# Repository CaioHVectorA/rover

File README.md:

# 🤖 Rover Móvel ESP32-S3 4WD & Pan/Tilt VR

Robô explorador terrestre com **tração integral 4WD**, cabeça articulada **Pan/Tilt** com streaming de vídeo de baixa latência e controle mobile imersivo via **Realidade Virtual (VR Head-Tracking)**.

---

### 🟢 Status do Projeto: **Robô montado & Testes práticos em andamento**
* **Hardware (V1 Montado):** Robô montado fisicamente (chassi 3D protótipo, rodas de 32 mm com 8 mm de vão livre, placa perfurada concluída).
* **Próxima Geração (PCB V2):** Transição direta para a PCB definitiva ([`rover_pcb_v2_chassi`](docs/hardware/kicad/rover_pcb_v2_chassi/MONTAGEM_3D.md)) com **ESP32 interno no chassi**, comunicação via **UART Serial Direta 3.3V** e áudio I2S (`INMP441` + `MAX98357A`).
* **Firmware & Visão:** ESP32-S3 e Nano operacionais com visão computacional (modo apresentador / gestos) em testes práticos.
* **Próximo passo:** Fabricar/montar a PCB V2, ajustar o chassi 3D para a nova placa e implementar o pipeline de vídeo UDP + servidor de IA.

---

## 🏗️ Arquitetura do Sistema

O projeto adota uma arquitetura **distribuída em 2 microcontroladores**, interligados por um chicote ultra-flexível de **apenas 3 a 4 fios**:

```mermaid
flowchart TD
    subgraph APP["📱 App Mobile (Expo / React Native) / Navegador Web"]
        VR["Modo VR Head-Tracking / FPV"]
        WS_CLI["WebSocket Client (JSON ou ASCII @ 35Hz)"]
        STREAM_CLI["Player de Vídeo MJPEG (:82/stream)"]
    end

    subgraph CABECA["📸 Cabeça Móvel (Pan / Tilt)"]
        ESP["ESP32-S3-CAM (Wi-Fi + Câmera 5MP OV5640)"]
        HTTPD["esp_http_server Dedicado no Core 0 (:82)"]
        CAM_PWR["Soneca Térmica no Reg. 0x3008"]
    end

    subgraph CHASSI["⚡ Chassi Fixo Inferior"]
        STEP["Mini 560 (5V / até 5A)"]
        BAT["Bateria Li-Ion 2S (7.4V 2500mAh)"]
        NANO["Arduino Nano V3 (5V Nativo)"]
        DRIVER["Driver TB6612FNG (MOSFET Duplo)"]
        MOTORES["4x Motores DC JGA16-050"]
        SERVOS["2x Micro Servos SG90 (Pan/Tilt)"]
        RAMPA["Rampa Soft-Start & Dead-Time"]
    end

    APP <== "Wi-Fi (Portas 80, 81 e 82)" ==> ESP
    BAT --> STEP
    BAT --> DRIVER

    %% Chicote Flexível
    STEP -.->|"Fio 1: 5.0V (Potência)"| ESP
    NANO -.->|"Fio 2: GND Comum"| ESP
    ESP -.->|"Fio 3: IO43 TX -> Nano D2 RX (via BC337 ou D0 direto)"| NANO
    NANO -.->|"Fio 4 (Opcional): Nano D1 TX -> Divisor 1k/2k -> IO44 RX"| ESP

    NANO --> DRIVER --> MOTORES
    NANO --> SERVOS
```

---

## 🔬 Suíte dos 6 POCs (Testes de Bancada Independentes)

Cada subsistema foi desacoplado para testes isolados e seguros:

| POC | Descrição | Placa & Ambiente | O que testa / resolve |
|---|---|---|---|
| **POC 1** | [Enlace Serial RX/TX](file:///c:/Users/caihe/Documents/develop/rover/docs/pocs/GUIA_EXECUCAO_POCS.md#poc-1-teste-de-enlace-serial-rxtx-com-servidor-web) | `poc1_esp32` + `poc1_nano` | Medição de ping/RTT, taxa de entrega de 100% e diagnóstico de reset do Nano |
| **POC 2** | [Pan/Tilt Controlado (Sem Vídeo)](file:///c:/Users/caihe/Documents/develop/rover/docs/pocs/GUIA_EXECUCAO_POCS.md#poc-2-pantilt-controlado-sem-v%C3%ADdeo) | `poc2_esp32` + `poc2_nano` | Eliminação do "rebolado" via interpolação em microssegundos (50 Hz) e varredura lenta |
| **POC 3** | [Transmissão de Vídeo Fria](file:///c:/Users/caihe/Documents/develop/rover/docs/pocs/GUIA_EXECUCAO_POCS.md#poc-3-transmiss%C3%A3o-de-v%C3%ADdeo-fria-esp32-isolado) | `poc3_esp32` | Soneca no reg. `0x3008`, XCLK adaptativo (8–12 MHz) e servidor no Core 0 (câmera fria) |
| **POC 4** | [Pan/Tilt + Transmissão](file:///c:/Users/caihe/Documents/develop/rover/docs/pocs/GUIA_EXECUCAO_POCS.md#poc-4-pantilt--transmiss%C3%A3o-desempenho-da-imagem) | `poc4_esp32` + `poc2_nano` | Operação simultânea com modo Eco automático (cai para 5 FPS parado) e zero bloqueio |
| **POC 5** | [Teste Automático dos Motores](file:///c:/Users/caihe/Documents/develop/rover/docs/pocs/GUIA_EXECUCAO_POCS.md#poc-5-teste-autom%C3%A1tico-de-motores-4wd-bancada-com-rodas-no-ar) | `poc5_nano` (baud 115200) | Sequência autônoma de vai-e-volta, giros e rampa com medição de queda (*sag*) de bateria |
| **POC 6** | [Motores Controlados](file:///c:/Users/caihe/Documents/develop/rover/docs/pocs/GUIA_EXECUCAO_POCS.md#poc-6-motores-controlados-joystick-virtual--teclado) | `poc6_esp32` + `poc6_nano` | Pilotagem manual (joystick touch / teclado WASD), watchdog de 600ms e rampa anti-reset |

📖 **Consulte o [Guia Completo de Execução dos POCs](file:///c:/Users/caihe/Documents/develop/rover/docs/pocs/GUIA_EXECUCAO_POCS.md)** para instruções de compilação, gravação e checklist.

---

## 📂 Organização Limpa da Codebase

```
rover/
├── README.md                      # Visão geral, arquitetura e quickstart
├── AGENTS.md                      # Diretrizes obrigatórias e regras para agentes de IA
├── style.md                       # Perfil de engenharia, tom de bancada e preferências
├── platformio.ini                 # Configuração unificada de build de todos os ambientes
│
├── docs/                          # Documentação técnica central
│   ├── context.md                 # 📖 Memória técnica contínua e histórico completo do projeto
│   ├── pocs/                      # Documentação da suíte de 6 POCs incrementais
│   │   ├── README.md              # Índice dos POCs e tabela de ambientes
│   │   └── GUIA_EXECUCAO_POCS.md  # Manual prático de gravação e teste passo a passo
│   ├── hardware/                  # Especificações técnicas, desenhos com cotas e pinagens
│   │   ├── ESPECIFICACOES_TECNICAS.md
│   │   ├── tabela_pinagem_esp32_nano.xlsx
│   │   ├── PROJETO_CONEXOES_PLACA_PERFURADA.docx
│   │   ├── kicad/                 # Projetos de circuitos e esquemáticos KiCad
│   │   └── *.png                  # Desenhos técnicos oficiais (JGA-050, SG90, StickyMAX)
│   ├── guides/                    # Guias de engenharia aprofundados
│   │   ├── camera_calor_software.md          # ❄️ Otimização térmica do OV5640 via software
│   │   ├── ajuste_fino_servos_rebolado.md    # 🎯 Física e eliminação do rebolado nos servos SG90
│   │   ├── tracao_motores_anti_reset.md      # ⚡ Prevenção de Brown-Out e rampa 4WD na TB6612
│   │   ├── controle_servos_head_tracking_vr.md # Guia didático de servos e VR Head-Tracking
│   │   ├── http_vs_websocket_redes.md        # Análise comparativa de protocolos de rede
│   │   └── streaming_video_baixa_latencia.md # Pipeline de vídeo MJPEG e baixa latência
│   ├── compras/                   # Histórico de compras, orçamentos e fotos das lojas
│   └── references/                # Fotos reais dos produtos e montagens maker de referência
│
├── src/                           # Código-fonte do projeto
│   ├── firmware/                  # Códigos C++ / Arduino organizados por módulo
│   │   ├── comum/                 # Módulos compartilhados reutilizáveis (câmera, enlace, rampa, servos)
│   │   ├── pocs/                  # Códigos-fonte dos 6 POCs isolados
│   │   ├── gateway_app/           # Firmware de produção integrado ao App Mobile Expo
│   │   └── legado/                # Sketches e testes históricos arquivados
│   ├── app_mobile/                # Aplicativo Expo / React Native (VR, FPV e Dashboard)
│   └── servidor_relay/            # Servidor Node.js / Docker para teleoperação em nuvem
│
└── tools/                         # Ferramentas auxiliares e geradores Python
    └── scratch/                   # Scripts utilitários de apoio
```

---

## ⚡ Comandos de Compilação e Gravação (PlatformIO)

Substitua `COMx` pelas portas seriais reais conectadas:

```powershell
# Gravação do ESP32-S3 (Exemplo POC 4: Pan/Tilt + Câmera):
pio run -e poc4_esp32 -t upload --upload-port COM24

# Gravação do Arduino Nano (Exemplo POC 2/4: Servos Suaves):
pio run -e poc2_nano -t upload --upload-port COM18

# Teste autônomo dos motores (POC 5):
pio run -e poc5_nano -t upload --upload-port COM18
pio device monitor -e poc5_nano --port COM18
```

---

## ⚙️ Componentes Físicos Adquiridos & Validados

| Componente | Modelo / Especificação | Função no Rover |
| :--- | :--- | :--- |
| **Motores de Tração** | 4x **JGA16-050** (16mm, redução metálica, eixo D 3mm) | Tração 4WD com torque elevado |
| **Rodas** | 4x **Rodas 32 mm** com cubo de fixação | Diâmetro externo de 32 mm elevando o vão livre para 8,0 mm |
| **Placa de Visão** | **ESP32-S3-CAM N16R8** (16MB Flash, 8MB PSRAM, OV5640 5MP) | Câmera, Wi-Fi e Streaming UDP Zero-Buffer |
| **Placa de Potência** | **Arduino Nano V3** (ATmega328P, 5V nativo) -> Migrando para **ESP32 DevKit V2** | Comanda TB6612, servos, buzzer e lê bateria |
| **Driver de Motores** | **TB6612FNG** (Ponte H MOSFET dupla, 1.2A/canal contínuo) | Controle de velocidade PWM e sentido 4WD |
| **Mecanismo Pan/Tilt** | 2x Micro Servos **SG90 9g** (Torque 1.6 kgf·cm) | Orientação horizontal e vertical da câmera |
| **Regulador de Tensão** | Step-Down **Mini 560** (5V fixos / até 5A) | Linha de 5V estável para placas e servos |
| **Bateria** | Li-Ion **2S 7.4V 2500mAh** com placa BMS integrada | Alimentação geral do robô |

> 📌 **Vão Livre ao Solo (Ground Clearance Real):**
> $$\text{Raio da Roda (16 mm)} - \text{Raio do Motor JGA (8 mm)} = \mathbf{8{,}0\text{ mm}}$$
> *A elevação para rodas de 32 mm resolveu o vão livre crítico de 3 mm das rodas de 22 mm anteriores, permitindo rodar em pisos reais sem raspar o motor.*

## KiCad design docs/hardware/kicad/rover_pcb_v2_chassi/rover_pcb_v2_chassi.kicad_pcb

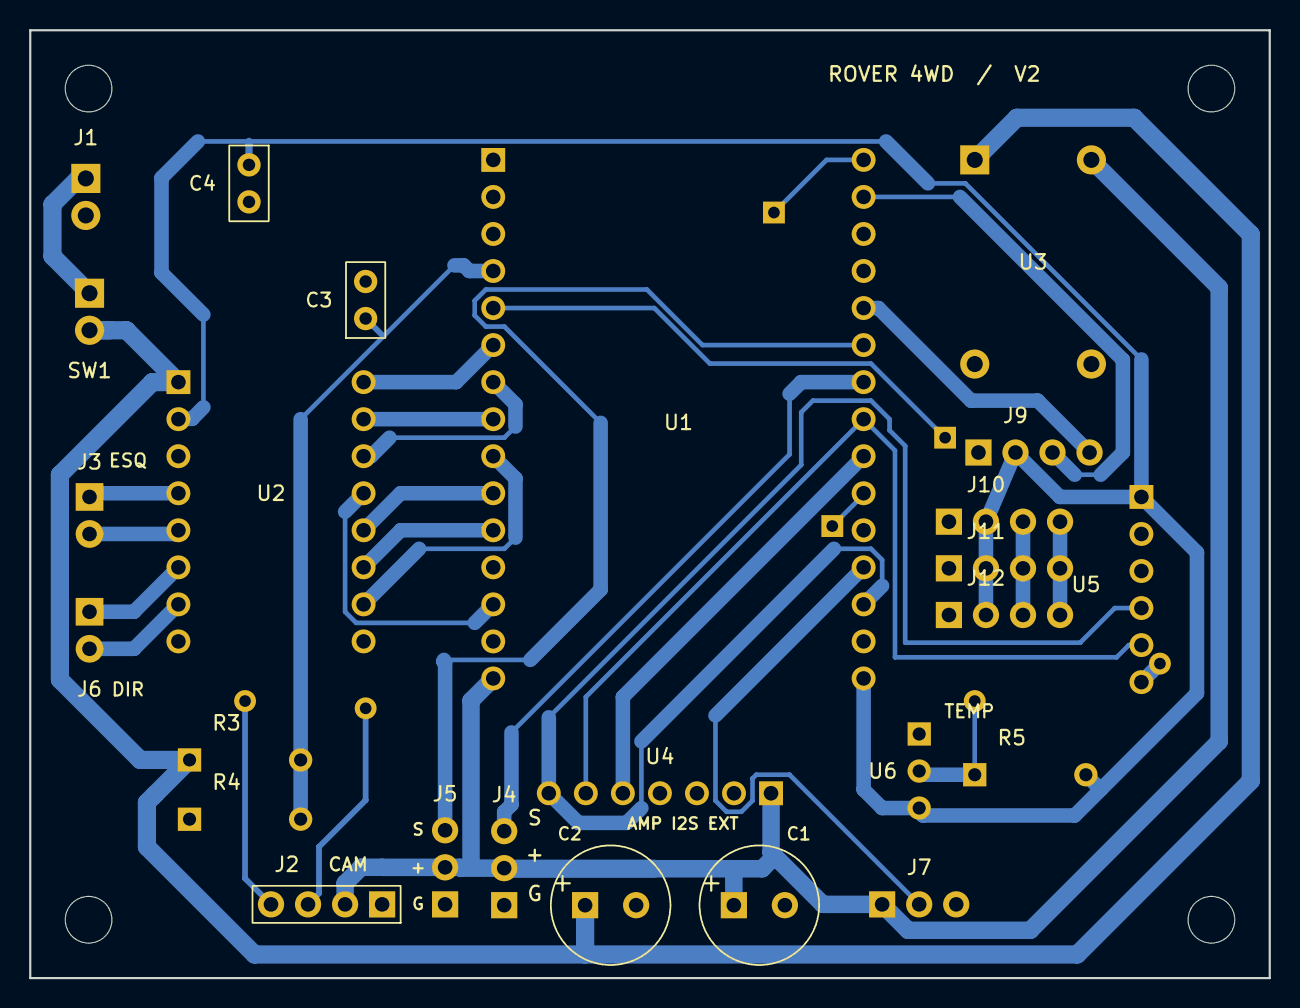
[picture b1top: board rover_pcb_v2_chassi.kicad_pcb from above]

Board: 2 copper layers, 85.0 x 65.0 mm, 35 parts (0 on the bottom side), 29 nets.

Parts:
C1: 470uF 16V; C_EL_P35
C2: 470uF 25V; C_EL_P35
C3, C4: 100nF; C_CER_P25
H1, H2, H3, H4: M3
J1: Bateria 2S; J1
J2: Camera UART 5V; J2
J3: Motor esquerdo; J3
J4: Servo PAN; J4
J5: Servo TILT; J5
J6: Motor direito; J6
J7: WS2812B; J7
J9: OLED I2C; J9
J10: I2C AUX 1; J9
J11: I2C AUX 2; J9
J12: I2C AUX 3; J9
JP1, JP2, JP3, JP4, JP5, JP6: FIO JUMPER ISOLADO; J3
R3: 10k; R3
R4: 4.7k; R4
R5: 4.7k; R5
SW1: Chave externa; SW1
U1: ESP32 DevKit V1 (30p); U1
U2: TB6612FNG; U2
U3: Mini 560; U3
U4: MAX98357A; U4
U5: INMP441; U5
U6: DS18B20; U6

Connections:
/+3V3: C4.1, J9.2 (+3V3), J10.2, J11.2, J12.2, R5.2, U1.1 (3V3), U2.2 (VCC), U5.1 (VDD), U6.3 (3V3)
/+5V: C1.1, J2.2, J4.2 (+5V), J5.2 (+5V), J7.1 (+5V), U1.30 (VIN), U3.3 (5V), U4.1 (Vin)
/BAT_RAW: J1.1 (BAT+), SW1.1 (IN)
/CAM-RX: J2.4, JP6.1, U1.15 (D23)
/CAM-TX: J2.3, JP5.1, U1.6 (RX2)
/GND: C1.2, C2.2, C3.2, C4.2, J1.2 (GND), J2.1, J4.1 (GND), J5.1 (GND), J7.3 (GND), J9.1 (GND), J10.1, J11.1, J12.1, R4.1, U1.2 (GND2), U1.29 (GND1), U2.3 (GND), U2.8 (GND2), U2.16 (GND3), U3.2 (IN-), U3.4 (GND), U4.2 (GND), U5.2 (GND), U5.3 (L/R), U6.1 (GND)
/I2S-BCLK: U1.8 (D5), U4.6 (BCLK), U5.5 (SCK)
/I2S-DIN: JP1.1 (I2S-DIN), U1.20 (D35), U5.6 (SD)
/I2S-DOUT: U1.7 (GPIO17 / TX2), U4.5 (DIN)
/I2S-WS: U1.3 (D15), U4.7 (LRC), U5.4 (WS)
/LED-DIN: J7.2 (LED-DIN), U1.4 (D2)
/MOT-AIN1: U1.22 (D33), U2.11 (AIN1)
/MOT-AIN2: U1.23 (D25), U2.10 (AIN2)
/MOT-BIN1: U1.25 (D27), U2.13 (BIN1)
/MOT-BIN2: U1.26 (D14), U2.14 (BIN2)
/MOT-PWMA: U1.21 (D32), U2.9 (PWMA)
/MOT-PWMB: U1.24 (D26), U2.15 (PWMB)
/MOT-STBY: U1.28 (D13), U2.12 (STBY)
/MOT_DIR_BO1: J6.2 (BO1), U2.7 (BO1)
/MOT_DIR_BO2: J6.1 (BO2), U2.6 (BO2)
/MOT_ESQ_AO1: J3.1 (AO1), U2.4 (AO1)
/MOT_ESQ_AO2: J3.2 (AO2), U2.5 (AO2)
/OLED-SCL: J9.3 (OLED-SCL), J10.3, J11.3, J12.3, JP4.1 (OLED-SCL), U1.14 (D22)
/OLED-SDA: J9.4 (OLED-SDA), J10.4, J11.4, J12.4, JP3.1 (OLED-SDA), U1.11 (D21)
/SERVO-PAN: J4.3 (SINAL), U1.9 (D18)
/SERVO-TILT: J5.3 (SINAL), U1.10 (D19)
/TEMP-DATA: JP2.1 (TEMP-DATA), R5.1, U1.5 (D4), U6.2 (DQ)
/VBAT-SENSE: C3.1, R3.2, R4.2, U1.19 (D34)
/VCC_BAT: C2.1, R3.1, SW1.2 (OUT), U2.1 (VM), U3.1 (IN+)

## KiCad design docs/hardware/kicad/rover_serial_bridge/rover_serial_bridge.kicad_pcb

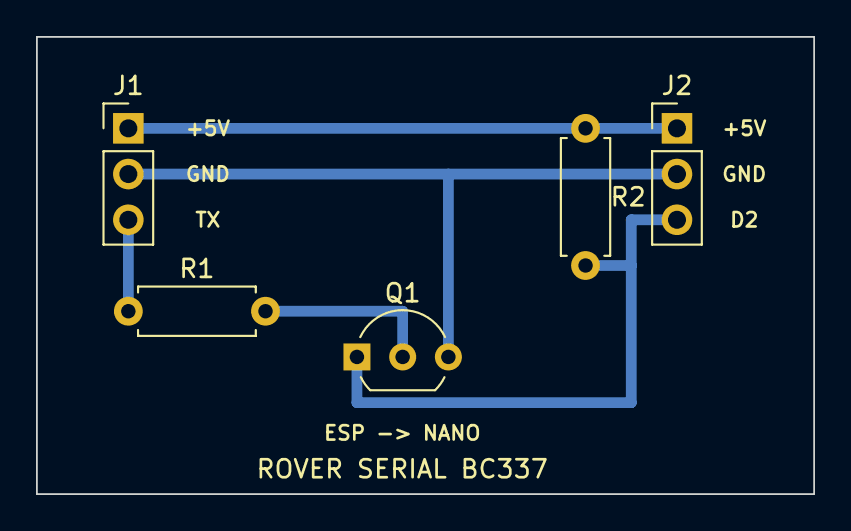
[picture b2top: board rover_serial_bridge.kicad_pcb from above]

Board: 2 copper layers, 43.2 x 25.4 mm, 5 parts (0 on the bottom side), 5 nets.

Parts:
J1: Cabeca_ESP; PinHeader_1x03_P2.54mm_Vertical
J2: Nano; PinHeader_1x03_P2.54mm_Vertical
Q1: BC337; TO-92_Inline_Wide
R1: 1k; R_Axial_DIN0207_L6.3mm_D2.5mm_P7.62mm_Horizontal
R2: 10k; R_Axial_DIN0207_L6.3mm_D2.5mm_P7.62mm_Horizontal

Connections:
+5V: J1.1, J2.1, R2.1
BASE_Q1: Q1.2, R1.2
ESP_TX_3V3: J1.3, R1.1
GND: J1.2, J2.2, Q1.3
NANO_D2: J2.3, Q1.1, R2.2

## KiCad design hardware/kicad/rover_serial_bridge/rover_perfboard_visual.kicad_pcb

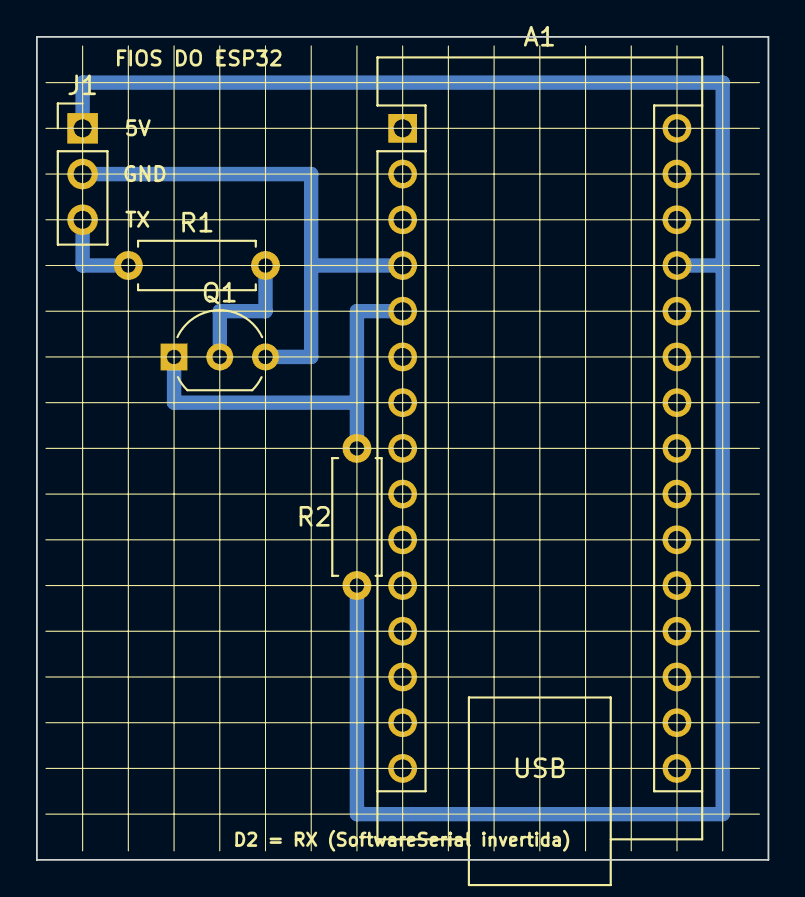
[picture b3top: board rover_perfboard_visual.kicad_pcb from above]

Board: 2 copper layers, 40.6 x 45.7 mm, 5 parts (0 on the bottom side), 5 nets.

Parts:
A1: Arduino Nano V3; Arduino_Nano
J1: Fios_do_ESP32; PinHeader_1x03_P2.54mm_Vertical
Q1: BC337; TO-92_Inline_Wide
R1: 1k; R_Axial_DIN0207_L6.3mm_D2.5mm_P7.62mm_Horizontal
R2: 10k; R_Axial_DIN0207_L6.3mm_D2.5mm_P7.62mm_Horizontal

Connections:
+5V: A1.27, J1.1, R2.1
BASE_Q1: Q1.2, R1.2
ESP_TX_3V3: J1.3, R1.1
GND: A1.4, A1.29, J1.2, Q1.3
NANO_D2: A1.5, Q1.1, R2.2
